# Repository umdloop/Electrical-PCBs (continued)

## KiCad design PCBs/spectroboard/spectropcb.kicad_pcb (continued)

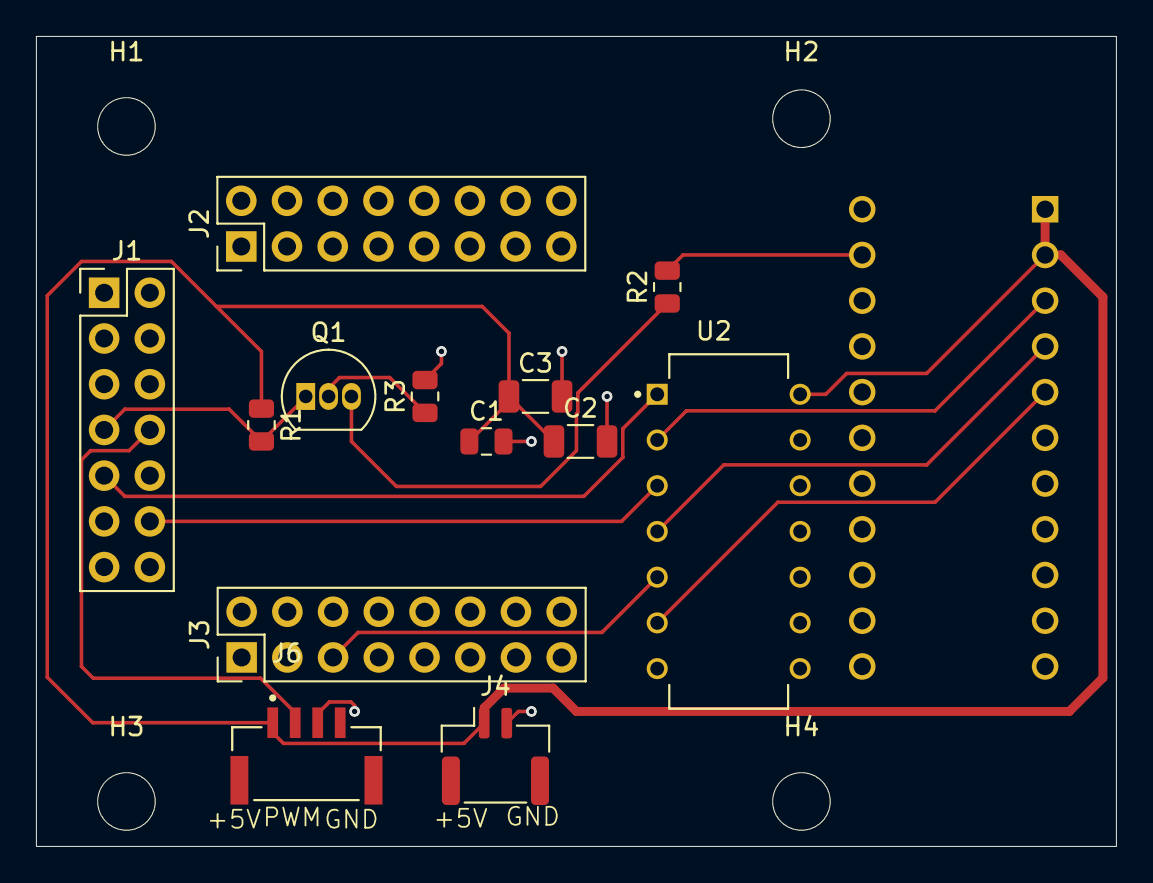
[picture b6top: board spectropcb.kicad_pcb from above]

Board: 2 copper layers, 60.0 x 45.0 mm, 18 parts (1 on the bottom side), 13 nets.

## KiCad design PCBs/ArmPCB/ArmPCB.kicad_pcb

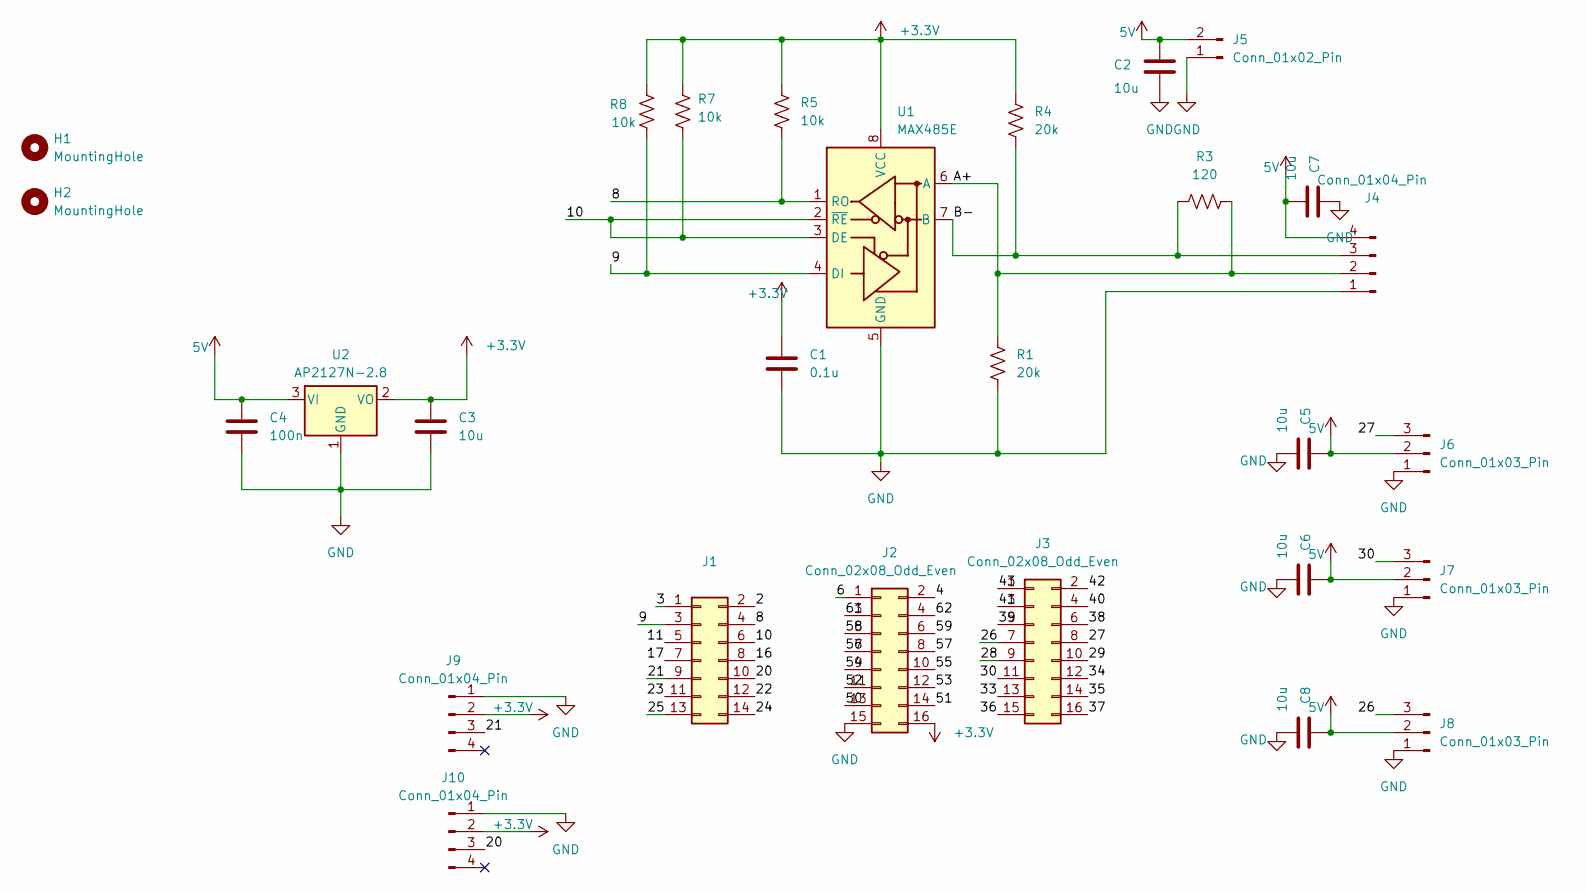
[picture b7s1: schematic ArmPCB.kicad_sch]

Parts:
C1: 0.1u; C_0402_1005Metric_Pad0.74x0.62mm_HandSolder
C2, C3, C5, C6, C7, C8: 10u; C_0402_1005Metric_Pad0.74x0.62mm_HandSolder
C4: 100n; C_0402_1005Metric_Pad0.74x0.62mm_HandSolder
H1, H2: MountingHole; MountingHole_3.2mm_M3_DIN965
J1: Conn_02x07_Odd_Even; PinHeader_2x07_P2.54mm_Vertical
J2, J3: Conn_02x08_Odd_Even; PinHeader_2x08_P2.54mm_Vertical
J4, J9, J10: Conn_01x04_Pin; JST_GH_SM04B-GHS-TB_1x04-1MP_P1.25mm_Horizontal
J5: Conn_01x02_Pin; JST_GH_SM02B-GHS-TB_1x02-1MP_P1.25mm_Horizontal
J6, J7, J8: Conn_01x03_Pin; JST_GH_SM03B-GHS-TB_1x03-1MP_P1.25mm_Horizontal
R1, R4: 20k; R_0402_1005Metric_Pad0.72x0.64mm_HandSolder
R3: 120; R_0402_1005Metric_Pad0.72x0.64mm_HandSolder
R5, R7, R8: 10k; R_0402_1005Metric_Pad0.72x0.64mm_HandSolder
U1: MAX485E; SOIC-8_3.9x4.9mm_P1.27mm
U2: AP2127N-2.8; SOT-223-3_TabPin2

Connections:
5V: C2.1, C4.1, C5.1, C6.1, C7.2, C8.1, J4.4, J5.2, J6.2, J7.2, J8.2, U2.3 (VI)
+3.3V: C1.1, C3.1, J2.16, J9.2, J10.2, R4.2, R5.1, R7.1, R8.1, U1.8 (VCC), U2.2 (VO)
/2: J1.2
/3: J1.1
/4: J2.2
/6: J2.1
/8: J1.4, R5.2, U1.1 (RO)
/9: J1.3, R8.2, U1.4 (DI)
/10: J1.6, R7.2, U1.2 (~RE), U1.3 (DE)
/11: J1.5
/16: J1.8
/17: J1.7
/20: J1.10, J10.3
/21: J1.9, J9.3
/22: J1.12
/23: J1.11
/24: J1.14
/25: J1.13
/26: J3.7, J8.3
/27: J3.8, J6.3
/28: J3.9
/29: J3.10
/30: J3.11, J7.3
/33: J3.13
/34: J3.12
/35: J3.14
/36: J3.15
/37: J3.16
/38: J3.6
/39: J3.5
/40: J3.4
/41: J3.3
/42: J3.2
/43: J3.1
/50: J2.13
/51: J2.14
/52: J2.11
/53: J2.12
/54: J2.9
/55: J2.10
/56: J2.7
/57: J2.8
/58: J2.5
/59: J2.6
/61: J2.3
/62: J2.4
/A+: J4.2, R1.1, R3.2, U1.6 (A)
/B-: J4.3, R3.1, R4.1, U1.7 (B)
GND: C1.2, C2.2, C3.2, C4.2, C5.2, C6.2, C7.1, C8.2, J2.15, J4.1, J5.1, J6.1, J7.1, J8.1, J9.1, J10.1, R1.2, U1.5 (GND), U2.1 (GND)

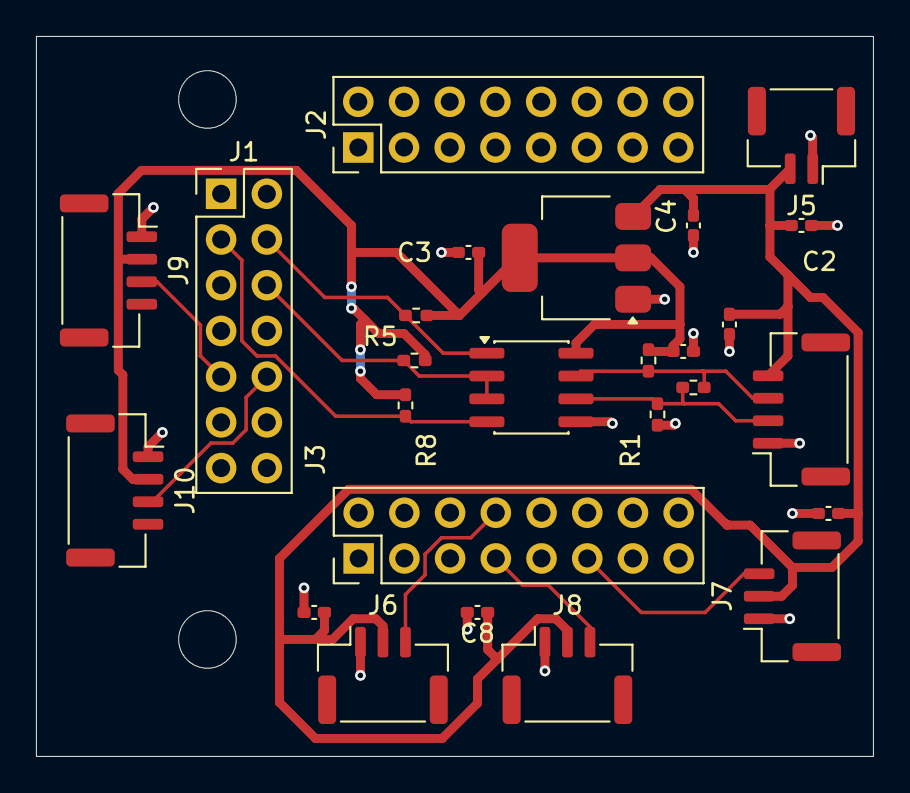
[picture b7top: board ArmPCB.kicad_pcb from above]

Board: 2 copper layers, 46.5 x 40.0 mm, 28 parts (0 on the bottom side), 13 nets.

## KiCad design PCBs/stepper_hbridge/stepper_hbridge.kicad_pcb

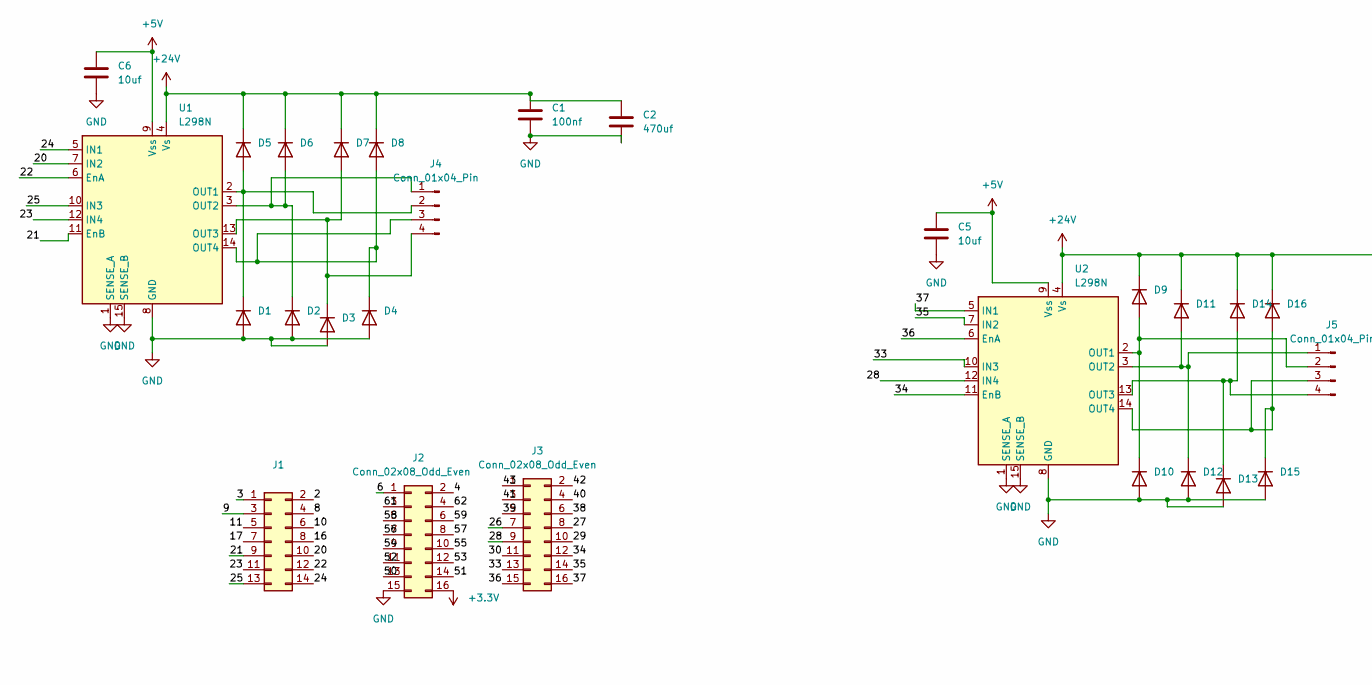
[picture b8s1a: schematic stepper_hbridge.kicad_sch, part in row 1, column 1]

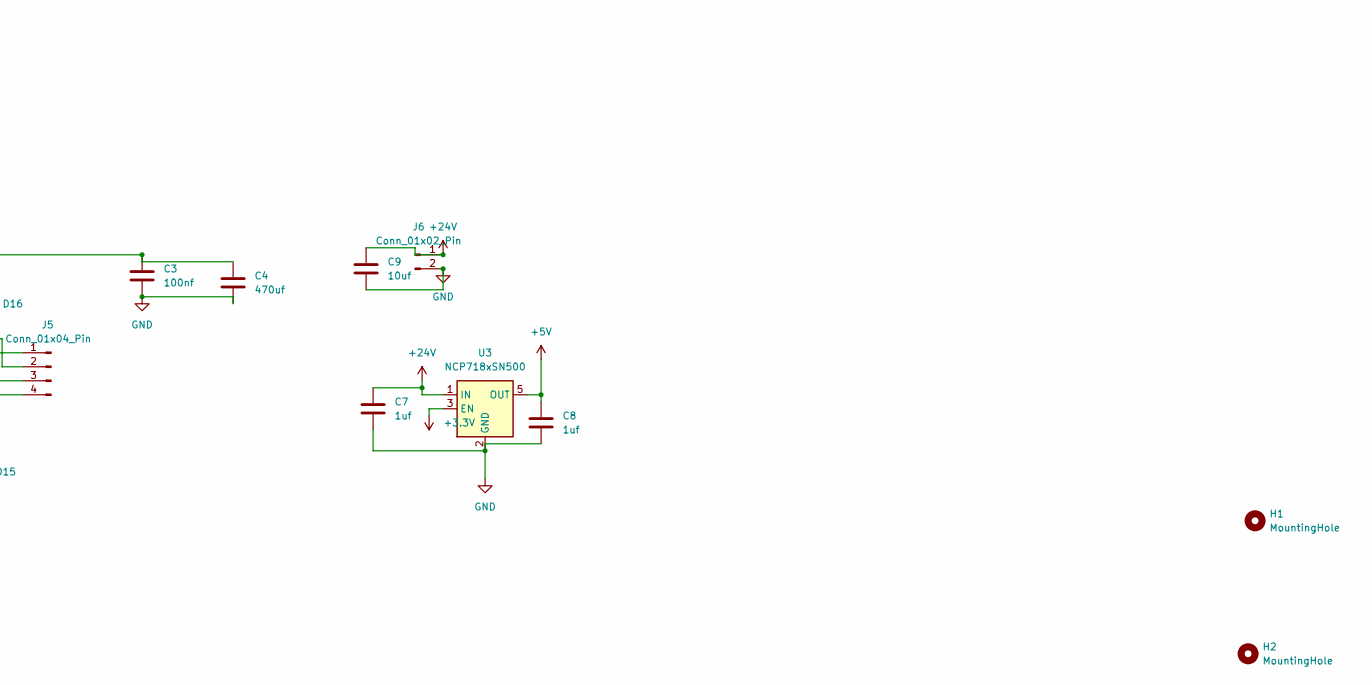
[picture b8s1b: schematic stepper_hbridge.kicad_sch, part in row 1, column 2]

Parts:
C1, C3: 100nf; C_0805_2012Metric_Pad1.18x1.45mm_HandSolder
C2, C4: 470uf; CP_Elec_6.3x7.7
C5, C6, C9: 10uf; C_0805_2012Metric_Pad1.18x1.45mm_HandSolder
C7, C8: 1uf; C_0805_2012Metric_Pad1.18x1.45mm_HandSolder
D1, D2, D3, D4, D5, D6, D7, D8, D9, D10, D11, D12, D13, D14, D15, D16: 1N4148WT; D_SOD-123
H1, H2: MountingHole; MountingHole_3.2mm_M3
J1: Conn_02x07_Odd_Even; PinHeader_2x07_P2.54mm_Vertical
J2, J3: Conn_02x08_Odd_Even; PinHeader_2x08_P2.54mm_Vertical
J4, J5: Conn_01x04_Pin; JST_GH_SM04B-GHS-TB_1x04-1MP_P1.25mm_Horizontal
J6: Conn_01x02_Pin; Molex_Micro-Fit_3.0_43045-0212_2x01_P3.00mm_Vertical
U1, U2: L298N; l298n_with_heatsink
U3: NCP718xSN500; SOT-23-5

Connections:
+3.3V: J2.16, U3.3 (EN)
+5V: C5.1, C6.1, C8.1, U1.9 (Vss), U2.9 (Vss), U3.5 (OUT)
+24V: C1.1, C2.1, C3.1, C4.1, C7.1, C9.1, D5.1 (K), D6.1 (K), D7.1 (K), D8.1 (K), D9.1 (K), D11.1 (K), D14.1 (K), D16.1 (K), J6.1, U1.4 (Vs), U2.4 (Vs), U3.1 (IN)
/2: J1.2
/3: J1.1
/4: J2.2
/6: J2.1
/8: J1.4
/9: J1.3
/10: J1.6
/11: J1.5
/16: J1.8
/17: J1.7
/20: J1.10, U1.7 (IN2)
/21: J1.9, U1.11 (EnB)
/22: J1.12, U1.6 (EnA)
/23: J1.11, U1.12 (IN4)
/24: J1.14, U1.5 (IN1)
/25: J1.13, U1.10 (IN3)
/26: J3.7
/27: J3.8
/28: J3.9, U2.12 (IN4)
/29: J3.10
/30: J3.11
/33: J3.13, U2.10 (IN3)
/34: J3.12, U2.11 (EnB)
/35: J3.14, U2.7 (IN2)
/36: J3.15, U2.6 (EnA)
/37: J3.16, U2.5 (IN1)
/38: J3.6
/39: J3.5
/40: J3.4
/41: J3.3
/42: J3.2
/43: J3.1
/50: J2.13
/51: J2.14
/52: J2.11
/53: J2.12
/54: J2.9
/55: J2.10
/56: J2.7
/57: J2.8
/58: J2.5
/59: J2.6
/61: J2.3
/62: J2.4
GND: C1.2, C2.2, C3.2, C4.2, C5.2, C6.2, C7.2, C8.2, C9.2, D1.2 (A), D2.2 (A), D3.2 (A), D4.2 (A), D10.2 (A), D12.2 (A), D13.2 (A), D15.2 (A), J2.15, J6.2, U1.1 (SENSE_A), U1.8 (GND), U1.15 (SENSE_B), U2.1 (SENSE_A), U2.8 (GND), U2.15 (SENSE_B), U3.2 (GND)
unnamed: D1.1 (K), D5.2 (A), J4.2, U1.2 (OUT1)
unnamed: D2.1 (K), D6.2 (A), J4.1, U1.3 (OUT2)
unnamed: D3.1 (K), D7.2 (A), J4.4, U1.13 (OUT3)
unnamed: D4.1 (K), D8.2 (A), J4.3, U1.14 (OUT4)
unnamed: D9.2 (A), D10.1 (K), J5.2, U2.2 (OUT1)
unnamed: D11.2 (A), D12.1 (K), J5.1, U2.3 (OUT2)
unnamed: D13.1 (K), D14.2 (A), J5.4, U2.13 (OUT3)
unnamed: D15.1 (K), D16.2 (A), J5.3, U2.14 (OUT4)

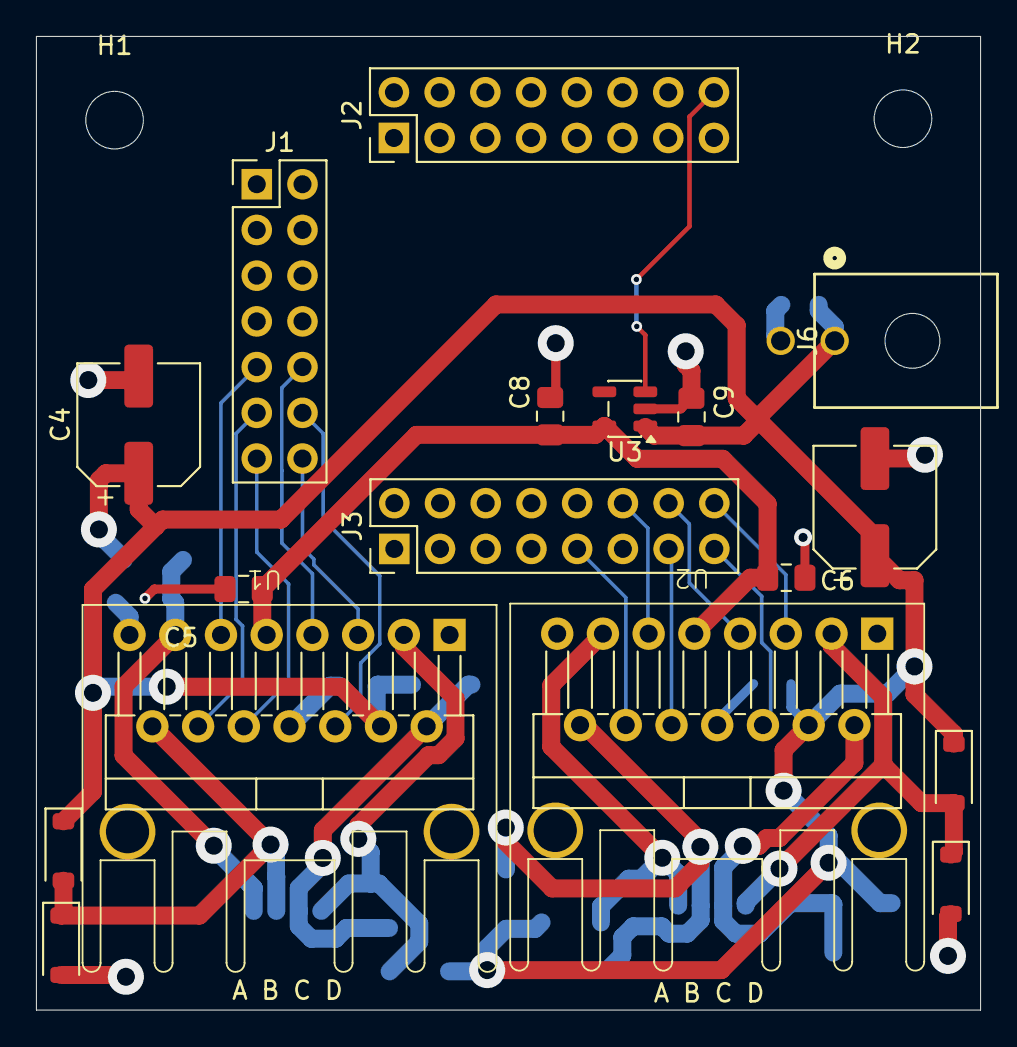
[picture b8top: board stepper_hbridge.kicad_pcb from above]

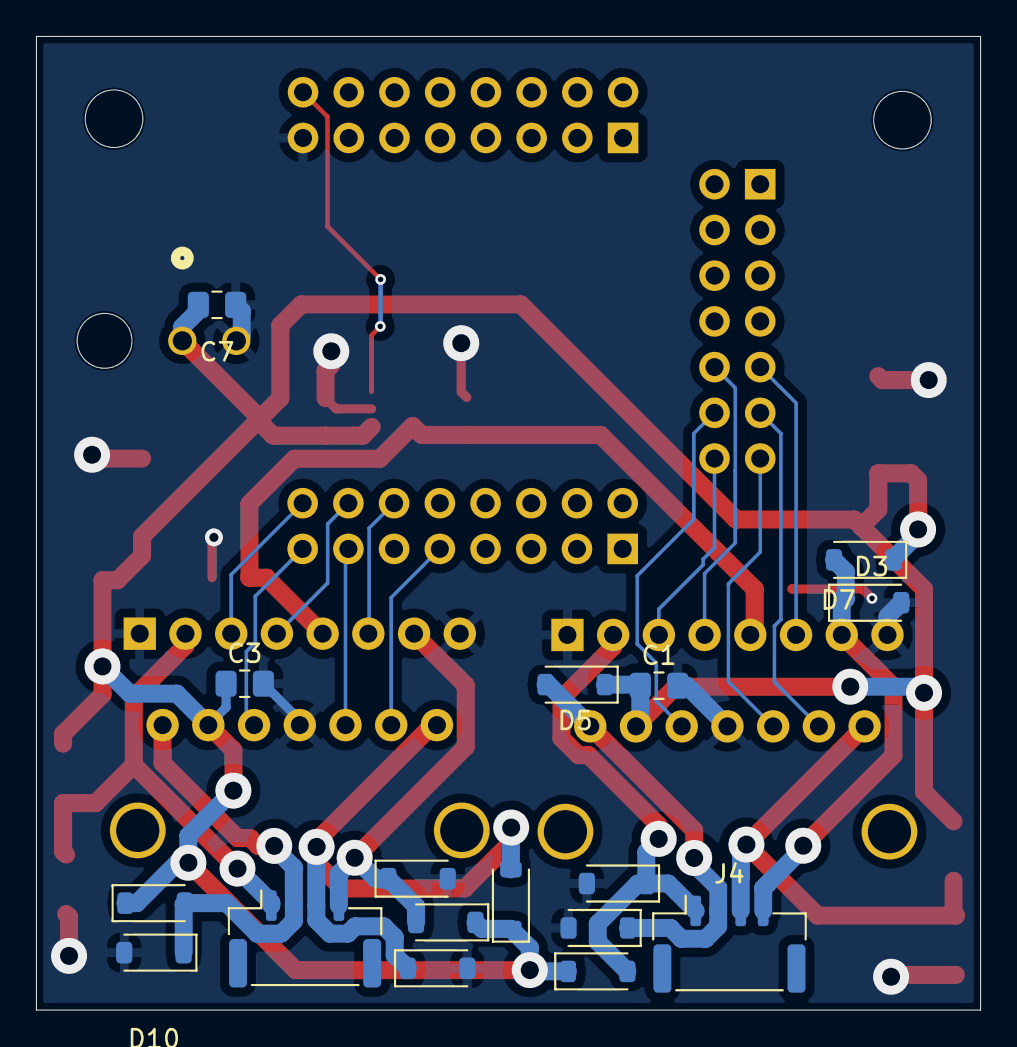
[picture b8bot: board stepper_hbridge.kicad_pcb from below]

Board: 2 copper layers, 52.5 x 54.1 mm, 36 parts (17 on the bottom side), 24 nets.

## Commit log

2026-03-11 Update README.md
    Modified the UMDLoop Athena Template to be about PCBs for this year's rover
2026-03-11 Update README.md
    updated again, adding more to "Including Libraries" section
2026-03-11 Adding power module PCB into GITHUB
    Adding power Module PCB into GITHUB
2026-03-11 Added directories for better organization
    Footprint_Libraries, Datasheets, and PCB Folders
2026-03-12 Added online_projects
    renamed everything to have same name
2026-03-12 updated power_module pcb
    updated power_module pcb
2026-03-23 umdloop_swerve added
2026-03-24 template added
2026-03-24 init 3DOF schematic
2026-03-25 updated with laser + servo + 485MAX (corrected
2026-03-25 reworded directory so people don't get confused
2026-03-25 stepper hbridge and dc motor pcbs done, still needs silksreen stuff, needs to be reviewed
2026-03-25 fixed errors, need to add quadrature
2026-03-25 fix RS485 + servo, add 10u cap's
2026-03-25 fix servos, add labels to schematic
2026-03-25 new name for "swerve"
2026-03-26 v1 power pcb w/ led level shifter
2026-03-28 minor fixes
2026-03-29 stepper - changed diode placement, changed JSTXH to GH, changed main 24V connector
2026-03-30 fixed both boards, just needs mounting + silkscreen, ready to review
2026-03-30 Base_Arm_PCB
    Base_ARM_PCB files for review
2026-03-30 Add spectrometer CCD PCB design
2026-03-30 finished draft of power_module, ready for review
2026-03-30 Edits to Stepper(H-Bridge)
2026-03-30 first thoughts
2026-03-30 added quadrature and mounting holes
2026-03-30 nothing
2026-03-30 both pcbs have smd capacitors, mounting holes, drc errors fixed
2026-03-31 review of base arm completed
2026-03-31 first revision
2026-03-31 added pin clarifications for Asgar
2026-03-31 revision 2: added c & r for snl, changed VccA to 3.3v
2026-03-31 added spectro Comments
2026-03-31 servo board for because it is still in use so it is relevant and neil needs it
2026-03-31 bug fixes
2026-04-01 modified according to feedback
2026-04-01 updated pcb
2026-04-01 removed silkscreen, ready for order
2026-04-01 silkscreen
2026-04-01 pinout checked, silkscreen added
2026-04-02 80% routed
2026-04-02 see 3DOF-testing, routing rough draft
2026-04-02 fixed 3.3V, fized header
2026-04-03 rename files
2026-04-05 3rd revision: corrected mounting holes
2026-04-05 mounting holes
2026-04-05 revision 4: shrunk board
2026-04-05 Base_Arm_PCB JST FIX
2026-04-05 Gerber_BaseArmPCB
2026-04-05 Arm_PCB_Gerber
2026-04-06 grounded ccd
2026-04-06 organized FLUORO into Main PCB Folder
2026-04-07 scapped power module pcb
2026-04-07 renamed directory Scrapped
2026-04-07 Added Power_module into Main
2026-04-07 init 2dof commit
2026-04-07 first review
2026-04-07 closed kicad
2026-04-07 intl fixes
2026-04-07 review2
2026-04-07 minor change in comments
2026-04-07 change servo folders
2026-04-07 more comments
2026-04-07 4 mounts
2026-04-07 revision 5: added mounting holes
2026-04-08 Changes to Fluoro
2026-04-08 cleaned up folders
2026-04-08 comments
2026-04-08 Fluoro PCB Changes
2026-04-08 Fluoro Changes
2026-04-08 2dof changes, cleaned up routing, fixed vias
2026-04-08 small fixes + comments
2026-04-09 RS485 fixes
2026-04-09 minor silkscreen fixes
2026-04-10 diode fixes
2026-04-12 3dmodel
2026-04-13 new 5V reg
2026-04-13 new 5V reg, closed kicad
2026-04-13 stlink
2026-04-13 make it look beautiful
2026-04-13 comments, ignore
2026-04-13 final (i think)
2026-04-19 3d models
2026-04-21 ground
2026-04-21 here u go asgar
2026-04-21 fixes :(((((((
2026-04-21 done
